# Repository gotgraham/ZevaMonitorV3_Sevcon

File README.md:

# ZevaMonitorV3_SevconGen4

This project is based on the now open source Zeva EVMS Monitor V3 from Ian Hooper. It has an MIT license as does Ian's original source.

It retains all the existing EVMS Monitor V3 features, and adds an additional screen for monitoring live parameters from a Sevcon Gen 4 controller.

- Motor Temp
- Motor RPM
- Controller Temp
- Velocity
- Phase Amps
- ...

To build:

Install avr-gcc

From the Firmware directory, run 'make all'. The makefile supports 'make all', 'make clean', and 'make flash'

Status:

 WIP

ZEVA EVMS Monitor V3
  Ian Hooper, August 2021

This archive contains all the files needed to reproduce the ZEVA EVMS Monitor V3, a touchscreen interface device for the EVMS3. Files are provided under the open source MIT license, found at the end of this file. The short version is that you may use these files for any purpose, free of charge, but they don’t come with any warranty or support.

PCB and schematic (.sch) files can be opened in Autodesk Eagle. If you don’t need to modify the design, the Gerber files in the PCB Assembly folder can be sent as-is to a PCB manufacturer to get boards made. Files for PCB assembly are also included, such as a Bill of Materials, centroid files (for pick-and-place machines), and example photos for reference. Parts in the Eagle file may not match the BoM in some cases. If in doubt, trust the BoM.

The LCD panels can be purchased off Alibaba or AliExpress - just search for “3.2 TFT LCD”, and look for pictures that match the example supplied with this download. Some example vendors are TZT, YTF, EQV, HESAI, Roarkit.

The firmware is written is C and can be compiled using AVR-GCC, normally using an IDE such as AVR / Microchip Studio. No claims are made about the quality or readability of the code. (This Monitor code in particular may be a bit of an impenetrable monolith if you’re not familiar with it - my apologies.) A precompiled HEX file is also supplied, which can be loaded onto boards as-is if standard firmware is suitable.

You will need an AVRISP type programming device for transferring firmware to the board, such as AVRISP MK2, STK500 or USBASP. The programming port on the PCB is a row of 5 holes near the microcontroller, with pin order GND, MOSI, MISO, SCK, RESET (with GND end marked). It is different to the usual 3x2 or 5x2 pin port used by AVRISP programmers, so you will need to make an adapter using 5 wires and some 0.1” pin header. Normally the 5x1 pin header can be pressed against the PCB holes during programming (avoids the need to add any connector to the board). The board will need to be powered during programming via 12V supplied to the CAN bus port.

AVR microcontrollers use “fuses” for setting things like the clock speed and brownout detection. The required fuse settings are listed near the top of the C code file.

There is a PCB support bracket that should be 3D printed, which gets fitted between the LCD module and the control board, and fastened to the control board using an M3x6 machine screw. Then the control board can be soldered to the 34x interface pins on the LCD module to complete the internal assembly. There are two housing options supplied, one panel mount which gets attached to the assembly using 4x M3x10 machine screws, or an enclosed housing with foot which gets screwed together using 4x M3x16 countersunk machine screws, and the foot can be attached using an M3x20 machine screw plus M3 nyloc nut. The mating connector for the CAN bus port is Molex 39500-0005. Remember to also fit jumpers to the two 2-pin headers either side of the CAN port, for the CAN termination resistor and to disable settings lock.

Once assembled and programmed, the EVMS Monitor should be ready to use. Please review the EVMS3 user manual for further information about installation and operation.

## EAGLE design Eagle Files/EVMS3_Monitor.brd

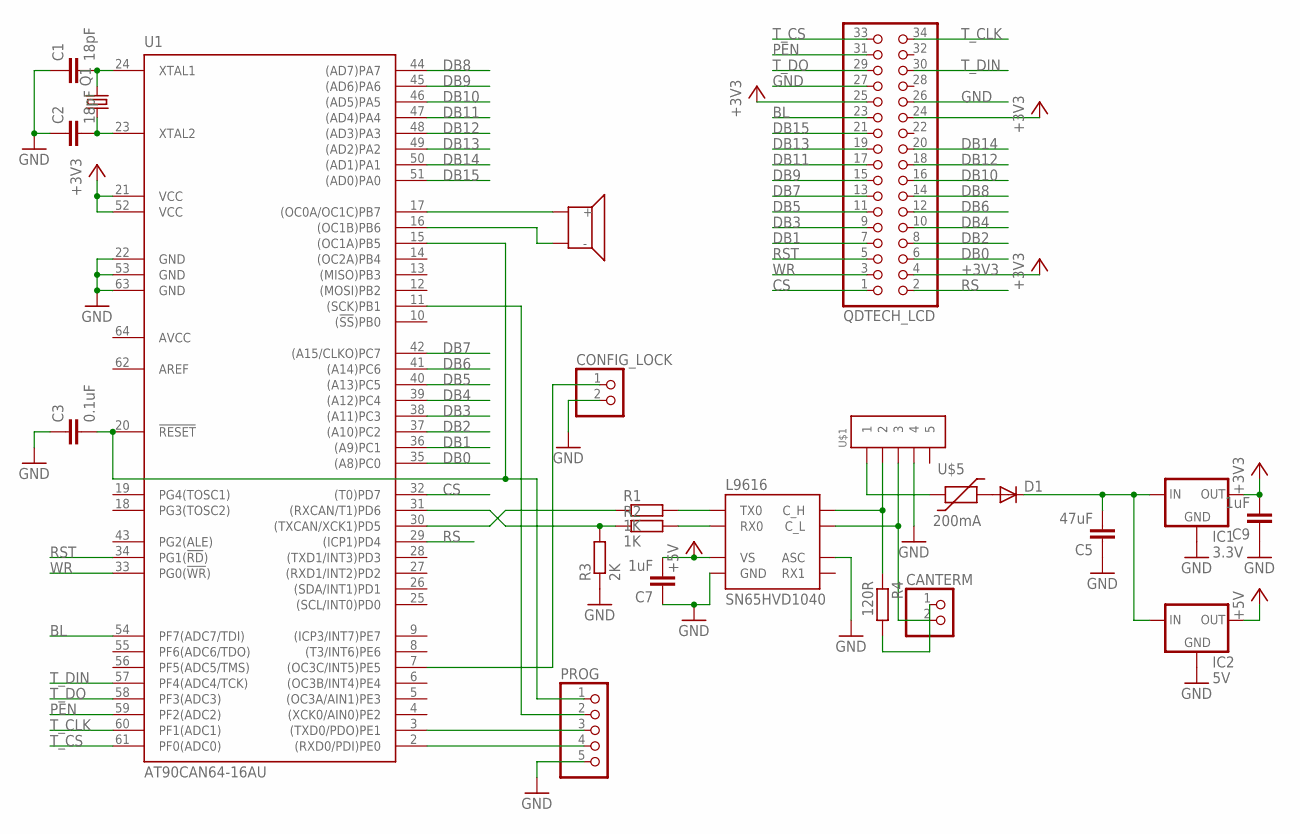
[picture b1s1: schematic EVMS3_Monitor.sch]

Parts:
C1, C2: 18pF; C0805
C3: 0.1uF; C1206
C5: 47uF; C1206
C7, C9: 1uF; C1206
CANTERM: PINHD-1X2; 1X02
CONFIG_LOCK: PINHD-1X2; 1X02
D1: DIODE-SOD123; SOD123
IC1: 3.3V; SOT89R
IC2: 5V; SOT89R
PROG: PINHD-1X5; 1X05
Q1: CRYSTALCTS406; CTS406
QDTECH_LCD: PINHD-2X17; 2X17
R1, R2: 1K; R1206
R3: 2K; R1206
R4: 120R; R1206
SN65HVD1040: L9616; SOIC8
U1: AT90CAN64-16AU; TQFP64-0.8MM
U$1: MOLEX-39502-1005VERT; MOLEX-39501-1005
U$5: 200mA; 1206
U$6: MURATA_PIEZO; PKLCS1212E_PIEZO

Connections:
+3V3: C9.2, IC1.2 (OUT), QDTECH_LCD.4, QDTECH_LCD.24, QDTECH_LCD.25, U1.21 (VCC), U1.52 (VCC)
+5V: C7.2, IC2.2 (OUT), SN65HVD1040.P$3 (VS)
AVCC: U1.64 (AVCC)
BL: QDTECH_LCD.23, U1.54 (PF7(ADC7/TDI))
BUZZER: U1.17 ((OC0A/OC1C)PB7), U$6.1 (+)
CS: QDTECH_LCD.1, U1.32 ((T0)PD7)
DB0: QDTECH_LCD.6, U1.35 ((A8)PC0)
DB1: QDTECH_LCD.7, U1.36 ((A9)PC1)
DB2: QDTECH_LCD.8, U1.37 ((A10)PC2)
DB3: QDTECH_LCD.9, U1.38 ((A11)PC3)
DB4: QDTECH_LCD.10, U1.39 ((A12)PC4)
DB5: QDTECH_LCD.11, U1.40 ((A13)PC5)
DB6: QDTECH_LCD.12, U1.41 ((A14)PC6)
DB7: QDTECH_LCD.13, U1.42 ((A15/CLKO)PC7)
DB8: QDTECH_LCD.14, U1.44 ((AD7)PA7)
DB9: QDTECH_LCD.15, U1.45 ((AD6)PA6)
DB10: QDTECH_LCD.16, U1.46 ((AD5)PA5)
DB11: QDTECH_LCD.17, U1.47 ((AD4)PA4)
DB12: QDTECH_LCD.18, U1.48 ((AD3)PA3)
DB13: QDTECH_LCD.19, U1.49 ((AD2)PA2)
DB14: QDTECH_LCD.20, U1.50 ((AD1)PA1)
DB15: QDTECH_LCD.21, U1.51 ((AD0)PA0)
GND: C1.1, C2.1, C3.1, C5.1, C7.1, C9.1, CONFIG_LOCK.2, IC1.4 (GND), IC2.4 (GND), PROG.5, QDTECH_LCD.26, QDTECH_LCD.27, R3.1, SN65HVD1040.P$2 (GND), SN65HVD1040.P$8 (ASC), U1.22 (GND), U1.53 (GND), U1.63 (GND), U$1.4
unnamed: C3.2, PROG.1, U1.15 ((OC1A)PB5), U1.20 (!RESET)
unnamed: C1.2, Q1.3 (2), U1.24 (XTAL1)
unnamed: C2.2, Q1.1, U1.23 (XTAL2)
unnamed: PROG.4, U1.2 ((RXD0/PDI)PE0)
unnamed: PROG.3, U1.3 ((TXD0/PDO)PE1)
unnamed: PROG.2, U1.11 ((SCK)PB1)
unnamed: R1.1, U1.30 ((TXCAN/XCK1)PD5)
unnamed: C5.2, D1.C, IC1.1 (IN), IC2.1 (IN)
unnamed: R2.1, R3.2, U1.31 ((RXCAN/T1)PD6)
unnamed: R1.2, SN65HVD1040.P$1 (TX0)
unnamed: R2.2, SN65HVD1040.P$4 (RX0)
unnamed: CONFIG_LOCK.1, U1.7 ((OC3C/INT5)PE5)
unnamed: R4.1, SN65HVD1040.P$7 (C_H), U$1.2
unnamed: CANTERM.2, SN65HVD1040.P$6 (C_L), U$1.3
unnamed: CANTERM.1, R4.2
unnamed: U1.16 ((OC1B)PB6), U$6.2 (-)
unnamed: D1.A, U$5.P$2
unnamed: U$1.1, U$5.P$1
PEN: QDTECH_LCD.31, U1.59 (PF2(ADC2))
RS: QDTECH_LCD.2, U1.29 ((ICP1)PD4)
RST: QDTECH_LCD.5, U1.34 (PG1(!RD!))
T_CLK: QDTECH_LCD.34, U1.60 (PF1(ADC1))
T_CS: QDTECH_LCD.33, U1.61 (PF0(ADC0))
T_DIN: QDTECH_LCD.30, U1.57 (PF4(ADC4/TCK))
T_DO: QDTECH_LCD.29, U1.58 (PF3(ADC3))
WR: QDTECH_LCD.3, U1.33 (PG0(!WR!))

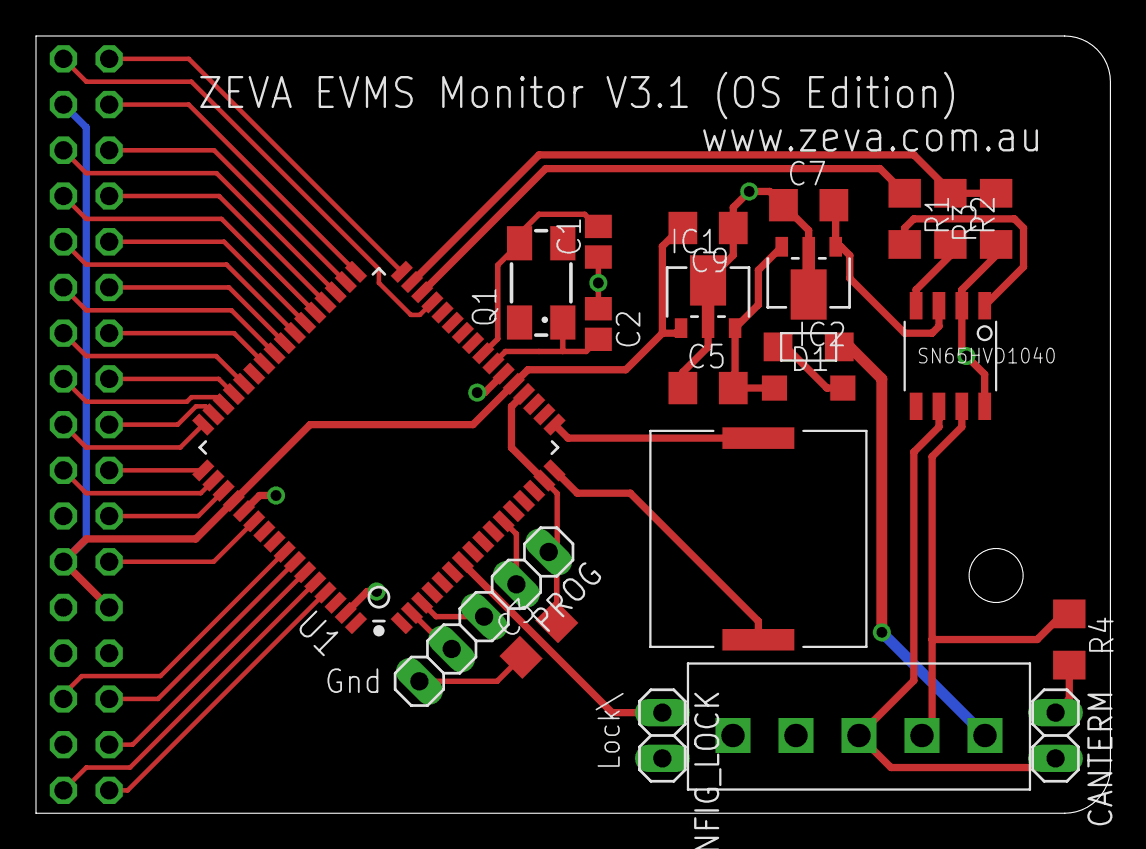
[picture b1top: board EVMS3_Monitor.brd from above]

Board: 2 copper layers, 59.7 x 43.2 mm, 23 parts (1 on the bottom side), 48 nets.

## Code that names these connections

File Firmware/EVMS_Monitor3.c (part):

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#define RUNNING_COLOUR	GREEN // RED
#define SOC_COLOUR		0		// or 0 to use green-to-red dynamic colouring

#define BUZZER	(1<<PB7)
#define BUZZER2	(1<<PB6)

#define CONFIG_LOCK	(PIND & (1<<PD0)) // Config lock normally pulled down (off) by jumper, i.e remove jumper to lock
#define CONFIG_LOCK2 (PINE & (1<<PE5)) // PCB version 3.1 reassigned this - but code should support both

#ifdef NEW_LCD
#define BACKLIGHT		(1<<PF7)
#define BACKLIGHT_PORT	PORTF
#define BACKLIGHT_DDR	DDRF
#else
#define BACKLIGHT		(1<<PD7)
#define BACKLIGHT_PORT	PORTD
#define BACKLIGHT_DDR	DDRD
#endif
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		}
	}
	else
		PORTB &= ~(BUZZER + BUZZER2); // Turn both off if not beeping
#else
	BACKLIGHT_PORT |= BACKLIGHT;
#endif
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	DDRG |= RST + WR;
	DDRD |= CS + RS + RD;
	PORTD |= (1<<PD0); // Pull up on config lock input
	PORTE |= (1<<PE5); // Pull up on new config lock input
#else
	DDRF |= RST + CS + RD + WR + RS; // LCD control pins
	DDRD |= (1<<PD0); // PD0 is config lock on the new LCD, but on the old one we have to just pull it low internally
	DDRE |= (1<<PE5); // As above, but for new config lock pin
#endif


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
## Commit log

2022-04-23 Initial
2022-04-23 Create LICENSE
2022-04-24 Set defaults to bike settings. Start framing in the motor page
2022-04-24 Switch to SoC and RPM on the motor page
2022-04-24 No need for the original image
2022-04-30 Start processing data from the sevcon
2022-05-02 Only show fractional amps when current is below 10a

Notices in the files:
Firmware/EVMS_Monitor3.c:
Open Source version, released under MIT License (see Readme file)
